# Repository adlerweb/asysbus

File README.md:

# aSysBus - The Arduino System Bus

aSysBus is hard- and software to build a network of arduino nodes using a CAN-bus or other interfaces. It was build as a replacement for [iSysBus<sup>(DE)</sup>](https://www.mikrocontroller.net/articles/Hausbus_Diskussion), which used native AVR code and a java based configuration framework instead of Arduino. It is mostly used for home automation and other control communication.

For CAN communication [Seeed-Studio/CAN_BUS_Shield](https://github.com/Seeed-Studio/CAN_BUS_Shield) is required. Be aware the library frequently breaks backwards compatibility. As time of writing master should work, if problems occur look for a commit close to a commit of this library and file a bug here.

Take a look around the wiki to learn more about the protocol, the included examples should help to get you started. If you speak german there are several videos over at [YouTube](https://www.youtube.com/user/adlerweb/search?query=aSysBus).

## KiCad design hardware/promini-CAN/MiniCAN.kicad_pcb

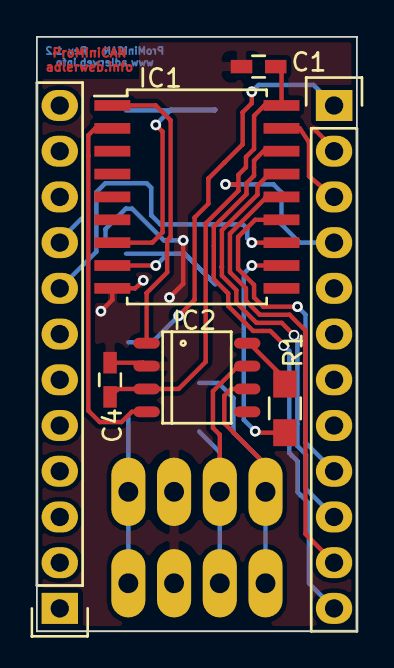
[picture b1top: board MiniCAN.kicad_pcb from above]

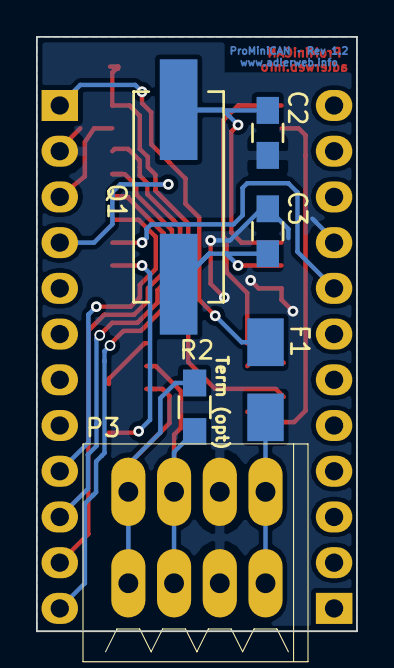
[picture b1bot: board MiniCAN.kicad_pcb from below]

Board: 2 copper layers, 17.8 x 33.0 mm, 13 parts (6 on the bottom side), 18 nets.

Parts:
C1, C4: 100nF; C_0603_HandSoldering
C2, C3: 22pF; C_0805_HandSoldering
F1: 160mA; Fuse_SMD1206_HandSoldering
IC1: MCP2515; SOIC-18_7.5x11.6mm_Pitch1.27mm
IC2: PCA 82C25x; SO-8
P1, P2: CONN_12; Pin_Header_Straight_1x12
P3: WAGO_233_504; WAGO_233-504
Q1: 16MHz/4MHz; Crystal_HC49-SD_SMD
R1: 82kΩ; R_0805_HandSoldering
R2: 120Ω; R_0805_HandSoldering

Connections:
+5V: C1.2, C4.2, IC1.18, IC2.3, P2.4
+12V: F1.1, P2.1
CAN_H: IC2.7, P3.2, R2.2
CAN_L: IC2.6, P3.1, R2.1
CS: IC1.16, P2.12
GND: C1.1, C2.1, C3.1, C4.1, IC1.9, IC2.2, P1.9, P2.2, P3.3
INT0: IC1.12, P1.8
MISO: IC1.15, P2.10
MOSI: IC1.14, P2.11
unnamed: C2.2, IC1.7, Q1.2
unnamed: C3.2, IC1.8, Q1.1
unnamed: F1.2, P3.4
unnamed: IC1.1, IC2.1
unnamed: IC1.2, IC2.4
unnamed: IC2.8, R1.1
RESET: IC1.17, P2.3
Rs: IC1.11, R1.2
SCK: IC1.13, P2.9

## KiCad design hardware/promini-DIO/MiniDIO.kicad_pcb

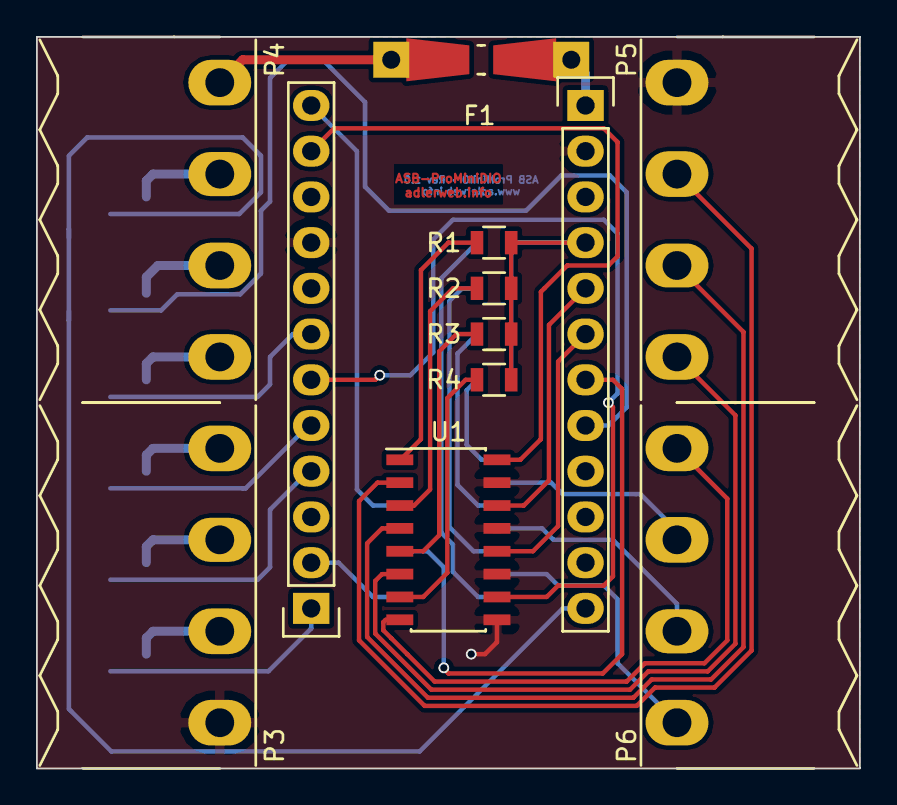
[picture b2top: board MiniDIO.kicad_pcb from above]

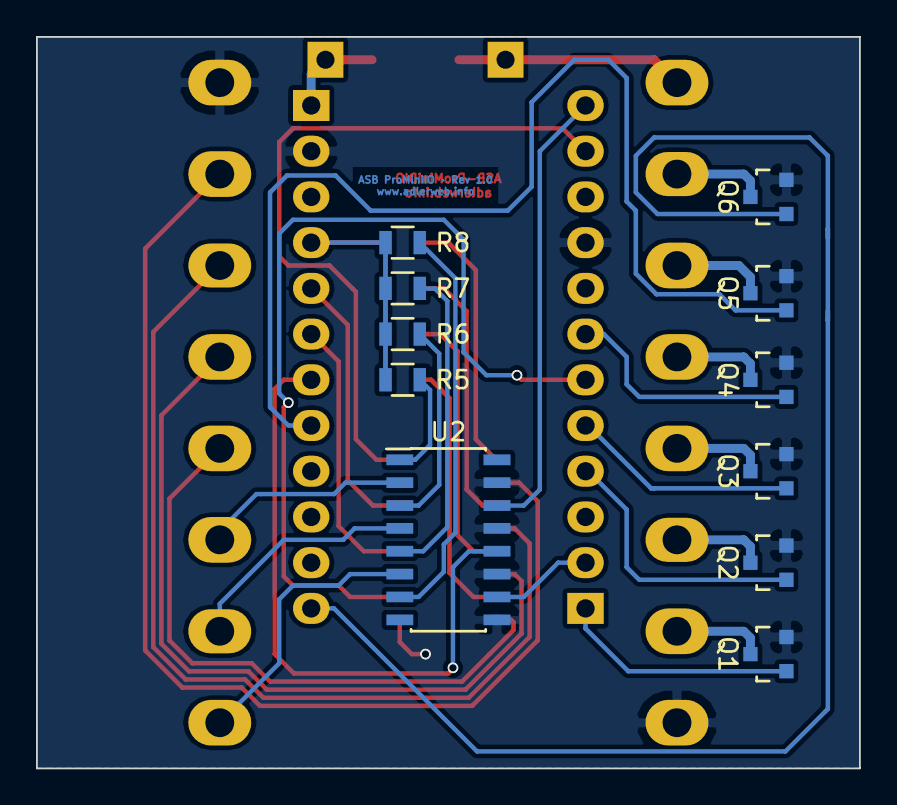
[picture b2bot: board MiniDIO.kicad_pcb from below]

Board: 2 copper layers, 45.7 x 40.6 mm, 23 parts (11 on the bottom side), 38 nets.

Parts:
F1: F_Small; Resistor_SMD+THTuniversal_0805to1206_RM10_HandSoldering
P1, P2: CONN_12; Pin_Header_Straight_1x12
P3, P4, P5, P6: CONN_01X04; WAGO_734_4pin_Straight_RuggedPads
Q1, Q2, Q3, Q4, Q5, Q6: Q_NMOS_GSD; SOT-23
R1, R2, R3, R4, R5, R6, R7, R8: 390; R_0805
U1, U2: PC847; SOIC-16_3.9x9.9mm_Pitch1.27mm

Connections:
+5V: P2.4, R1.2, R2.2, R3.2, R4.2, R5.2, R6.2, R7.2, R8.2
+12V: F1.2, P4.1
GND: P1.9, P2.2, P3.4, P5.4, Q1.2, Q2.2, Q3.2, Q4.2, Q5.2, Q6.2, U1.9, U1.11, U1.13, U1.15, U2.9, U2.11, U2.13, U2.15
unnamed: F1.1, P2.1
unnamed: P1.1, Q1.1
unnamed: P1.2, U2.10
unnamed: P1.4, Q2.1
unnamed: P1.5, Q3.1
unnamed: P1.6, U1.10
unnamed: P1.7, Q4.1
unnamed: P1.11, U1.16
unnamed: P1.12, U2.14
unnamed: P2.5, U1.14
unnamed: P2.6, U1.12
unnamed: P2.7, U2.12
unnamed: P2.8, Q5.1
unnamed: P2.12, Q6.1
unnamed: P3.1, Q3.3
unnamed: P3.2, Q2.3
unnamed: P3.3, Q1.3
unnamed: P4.2, Q6.3
unnamed: P4.3, Q5.3
unnamed: P4.4, Q4.3
unnamed: P5.1, U1.6
unnamed: P5.2, U1.4
unnamed: P5.3, U1.2
unnamed: P6.1, U2.6
unnamed: P6.2, U2.4
unnamed: P6.3, U2.2
unnamed: P6.4, U1.8
unnamed: R1.1, U1.1
unnamed: R2.1, U1.3
unnamed: R3.1, U1.5
unnamed: R4.1, U1.7
unnamed: R5.1, U2.1
unnamed: R6.1, U2.3
unnamed: R7.1, U2.5
unnamed: R8.1, U2.7

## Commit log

2017-07-01 Import library
2017-07-02 Add hardware
2017-08-09 UART: Input hex parser
    Input did only accept numeric values instead of the desired hex. Thanks
    to Adrian for the report.
2017-12-03 Tried to fix breaking changes caused by upgrade to current master of "Seeed-Studio/CAN_BUS_Shield" library (358aaace91dfe6a34eb4ffc4af68a3ab85ed359e); Also set all example sketches to consistent CAN 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
2017-12-03 Fixed overflow issue in "simple" example
2018-01-14 Allow using upstream Seeed-Studio/CAN_BUS_Shield library
    Based on #1
2018-01-14 Make data const byte *
    Based on #1
2018-01-14 Python decoder
2018-01-14 Python Encoder
2018-01-14 MQTT gateway test script
2018-03-17 MQTT: Catch more errors, example for TLS/Password
2018-06-15 README: Typo
2018-07-01 Redme: Link to CAN_BUS_Shield
    ref #3, #6
2018-11-04 busId is never negative -> unsigned
2018-11-04 Remove unused variables
2018-11-04 always return something if function isn't void
2018-11-04 Improved module attach
2018-11-04 Corrected inline documentation
2018-11-04 Avoid double-free, should fix #5
2018-11-04 Add python asyncio MQTT proxy script
2018-11-04 MQTT proxy requirements
2018-11-24 Remove invalid code
    A bad line sneaked in with commit 5ca27173cf68428797a1ddf957d06e1fbf3c831a, causing the library to fail compiling. Let's remove it again and fix #10
2018-12-04 busId is negative to indicate invalid packets revert 4e42fe3d97914d60e6f423ca06f55561b40b082c
2018-12-04 Abort attach if bus signals a problem Could help in case of #2
2018-12-04 Drop reading rtr/ext due to a problem with extended readMsgBufID Currently using readMsgBufID will not correctly signal "no packet" and runs into a loop Ref #8
2018-12-04 Lastboot causes IndexError
2018-12-04 Improved MQTT-TX error handling
2022-07-25 CAN: unable to parse UNICASE
    #12
2023-04-11 mqtt-proxy: Python >=3.10
    Python >=3.10 does no longer support loop parameter
    https://docs.python.org/3/library/asyncio-stream.html
